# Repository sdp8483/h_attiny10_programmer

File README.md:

# ATTINY10 High Voltage Programmer
based on design from Ben Hecks video: https://www.youtube.com/watch?v=ra7bT74EGUs&t=913s

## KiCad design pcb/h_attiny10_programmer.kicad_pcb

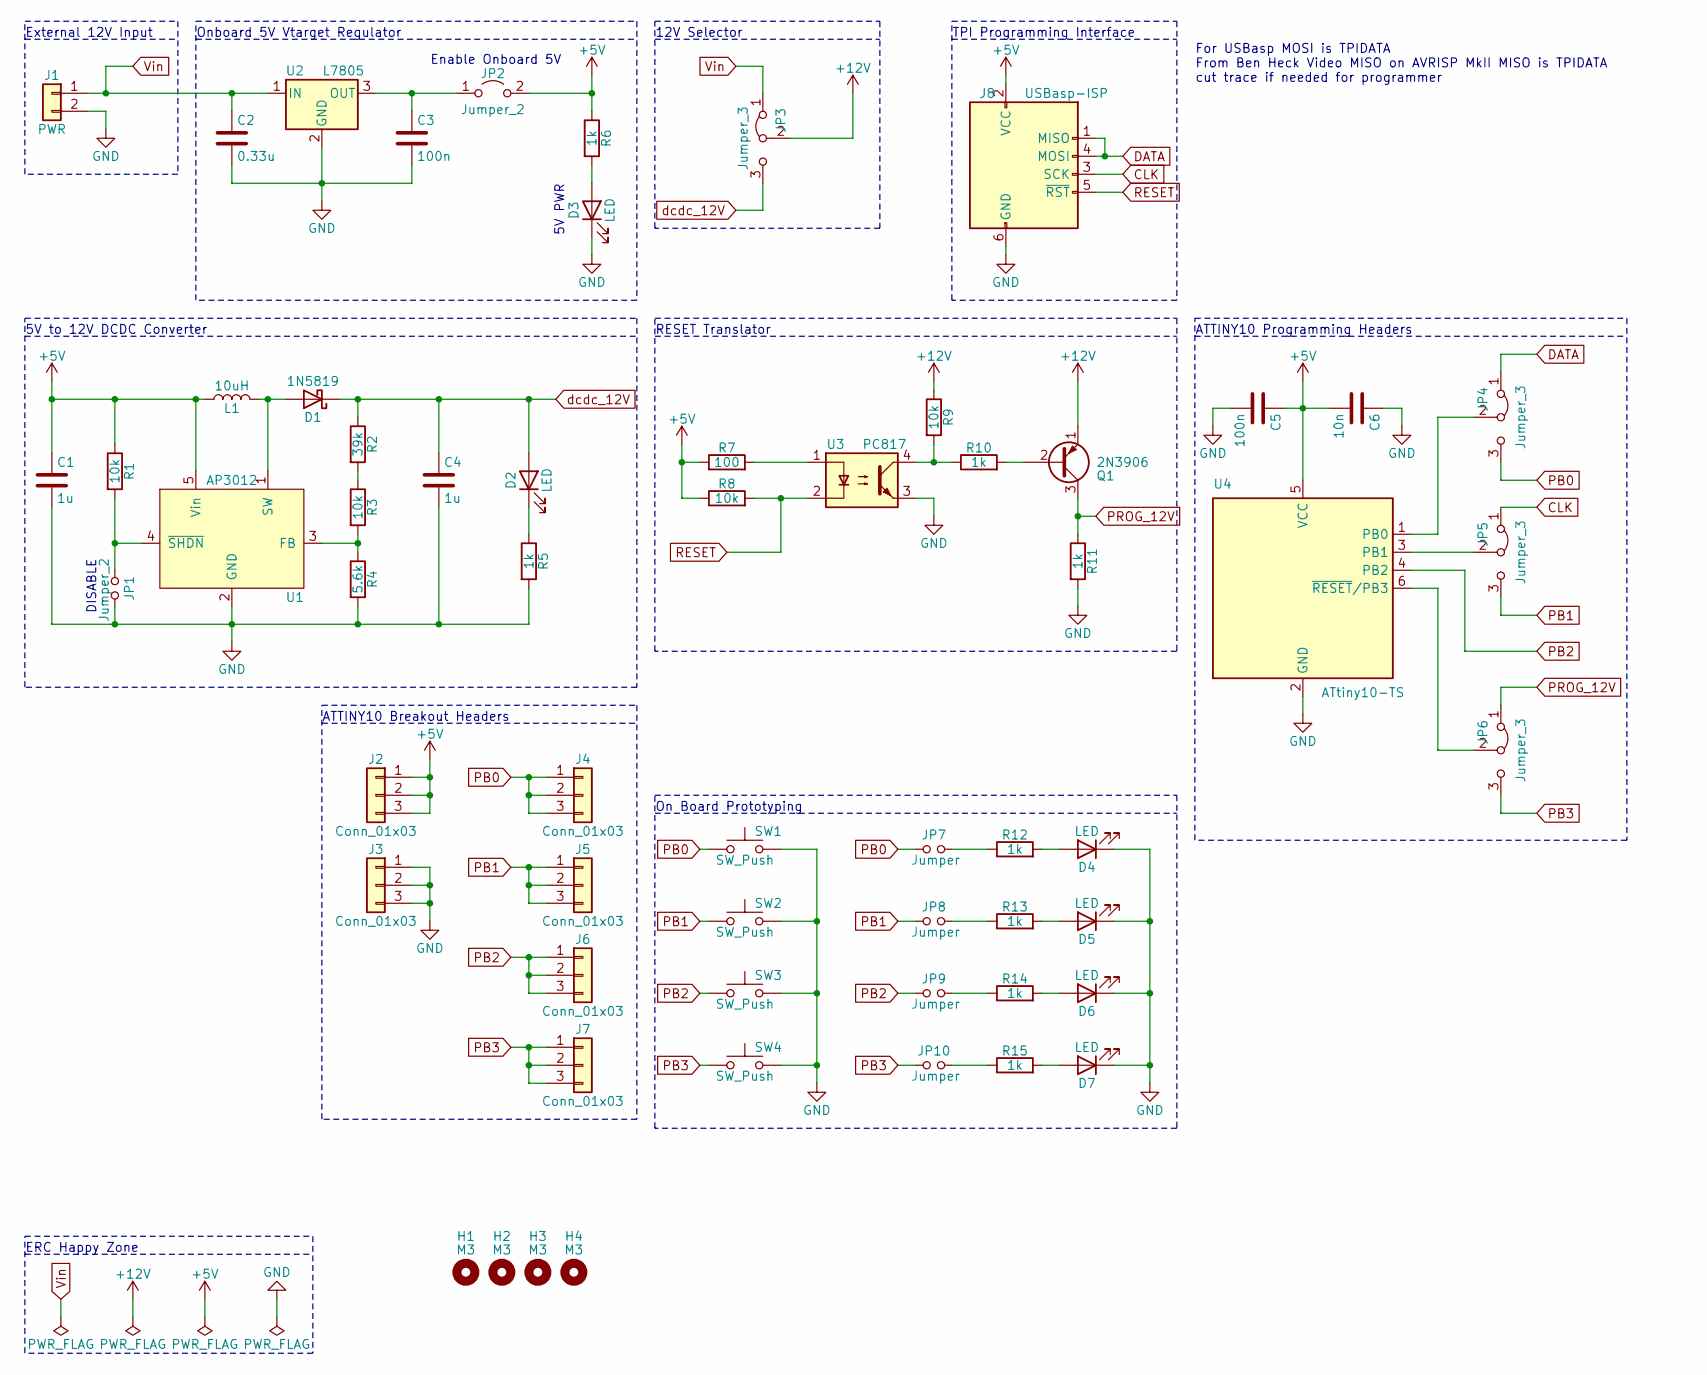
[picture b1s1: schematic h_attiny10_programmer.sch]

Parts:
C1, C4: 1u; C_0805_2012Metric_Pad1.18x1.45mm_HandSolder
C2: 0.33u; CP_Radial_D5.0mm_P2.50mm
C3: 100n; C_Disc_D4.3mm_W1.9mm_P5.00mm
C5: 100n; C_0805_2012Metric_Pad1.18x1.45mm_HandSolder
C6: 10n; C_0805_2012Metric_Pad1.18x1.45mm_HandSolder
D1: 1N5819; D_DO-41_SOD81_P10.16mm_Horizontal
D2, D3, D4, D5, D6, D7: LED; LED_D5.0mm
H1, H2, H3, H4: M3; MountingHole_3.5mm
J1: PWR; TerminalBlock_bornier-2_P5.08mm
J2, J3, J4, J5, J6, J7: Conn_01x03; PinHeader_1x03_P2.54mm_Vertical
J8: USBasp-ISP; PinHeader_2x03_P2.54mm_Vertical
JP1, JP2: Jumper_2; PinHeader_1x02_P2.54mm_Vertical
JP3, JP4, JP5, JP6: Jumper_3; PinHeader_1x03_P2.54mm_Vertical
JP7, JP8, JP9, JP10: Jumper; PinHeader_1x02_P2.54mm_Vertical
L1: 10uH; sumida_cdrh2d11
Q1: 2N3906; TO-92_Inline_Wide
R1, R3, R8, R9: 10k; R_Axial_DIN0207_L6.3mm_D2.5mm_P10.16mm_Horizontal
R2: 39k; R_Axial_DIN0207_L6.3mm_D2.5mm_P10.16mm_Horizontal
R4: 5.6k; R_Axial_DIN0207_L6.3mm_D2.5mm_P10.16mm_Horizontal
R5, R6, R10, R11, R12, R13, R14, R15: 1k; R_Axial_DIN0207_L6.3mm_D2.5mm_P10.16mm_Horizontal
R7: 100; R_Axial_DIN0207_L6.3mm_D2.5mm_P10.16mm_Horizontal
SW1, SW2, SW3, SW4: SW_Push; SW_PUSH_6mm
U1: AP3012; SOT-23-5
U2: L7805; TO-220-3_Vertical
U3: PC817; DIP-4_W7.62mm
U4: ATtiny10-TS; DIP-6_W7.62mm

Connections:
+5V: C1.1, C5.1, C6.2, J2.1, J2.2, J2.3, J8.2 (VCC), JP2.2 (B), L1.2, R1.1, R6.1, R7.1, R8.1, U1.5 (Vin), U4.5 (VCC)
+12V: JP3.2 (C), Q1.1 (E), R9.1
CLK: J8.3 (SCK), JP5.1 (A)
DATA: J8.1 (MISO), J8.4 (MOSI), JP4.1 (A)
GND: C1.2, C2.2, C3.2, C4.2, C5.2, C6.1, D3.1 (K), D4.1 (K), D5.1 (K), D6.1 (K), D7.1 (K), J1.2, J3.1, J3.2, J3.3, J8.6 (GND), JP1.2, R4.2, R5.2, R11.2, SW1.2, SW2.2, SW3.2, SW4.2, U1.2 (GND), U2.2 (GND), U3.3, U4.2 (GND)
unnamed: C3.1, JP2.1 (A), U2.3 (OUT)
unnamed: D1.2 (A), L1.1, U1.1 (SW)
unnamed: D2.1 (K), R5.1
unnamed: D3.2 (A), R6.2
unnamed: D4.2 (A), R12.2
unnamed: D5.2 (A), R13.2
unnamed: D6.2 (A), R14.2
unnamed: D7.2 (A), R15.2
unnamed: JP1.1, R1.2, U1.4 (~SHDN)
unnamed: JP4.2 (C), U4.1 (PB0)
unnamed: JP5.2 (C), U4.3 (PB1)
unnamed: JP6.2 (C), U4.6 (~RESET~/PB3)
unnamed: JP7.2, R12.1
unnamed: JP8.2, R13.1
unnamed: JP9.2, R14.1
unnamed: JP10.2, R15.1
unnamed: Q1.2 (B), R10.2
unnamed: R2.2, R3.1
unnamed: R3.2, R4.1, U1.3 (FB)
unnamed: R7.2, U3.1
unnamed: R9.2, R10.1, U3.4
PB0: J4.1, J4.2, J4.3, JP4.3 (B), JP7.1, SW1.1
PB1: J5.1, J5.2, J5.3, JP5.3 (B), JP8.1, SW2.1
PB2: J6.1, J6.2, J6.3, JP9.1, SW3.1, U4.4 (PB2)
PB3: J7.1, J7.2, J7.3, JP6.3 (B), JP10.1, SW4.1
PROG_12V: JP6.1 (A), Q1.3 (C), R11.1
RESET: J8.5 (~RST), R8.2, U3.2
Vin: C2.1, J1.1, JP3.1 (A), U2.1 (IN)
dcdc_12V: C4.1, D1.1 (K), D2.2 (A), JP3.3 (B), R2.1

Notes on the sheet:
External 12V Input
Onboard 5V Vtarget Regulator
5V to 12V DCDC Converter
12V Selector
5V PWR
Enable Onboard 5V
ATTINY10 Programming Headers
RESET Translator
TPI Programming Interface
ATTINY10 Breakout Headers
On Board Prototyping
DISABLE
ERC Happy Zone
For USBasp MOSI is TPIDATA From Ben Heck Video MISO on AVRISP MkII MISO is TPIDATA cut trace if needed for programmer

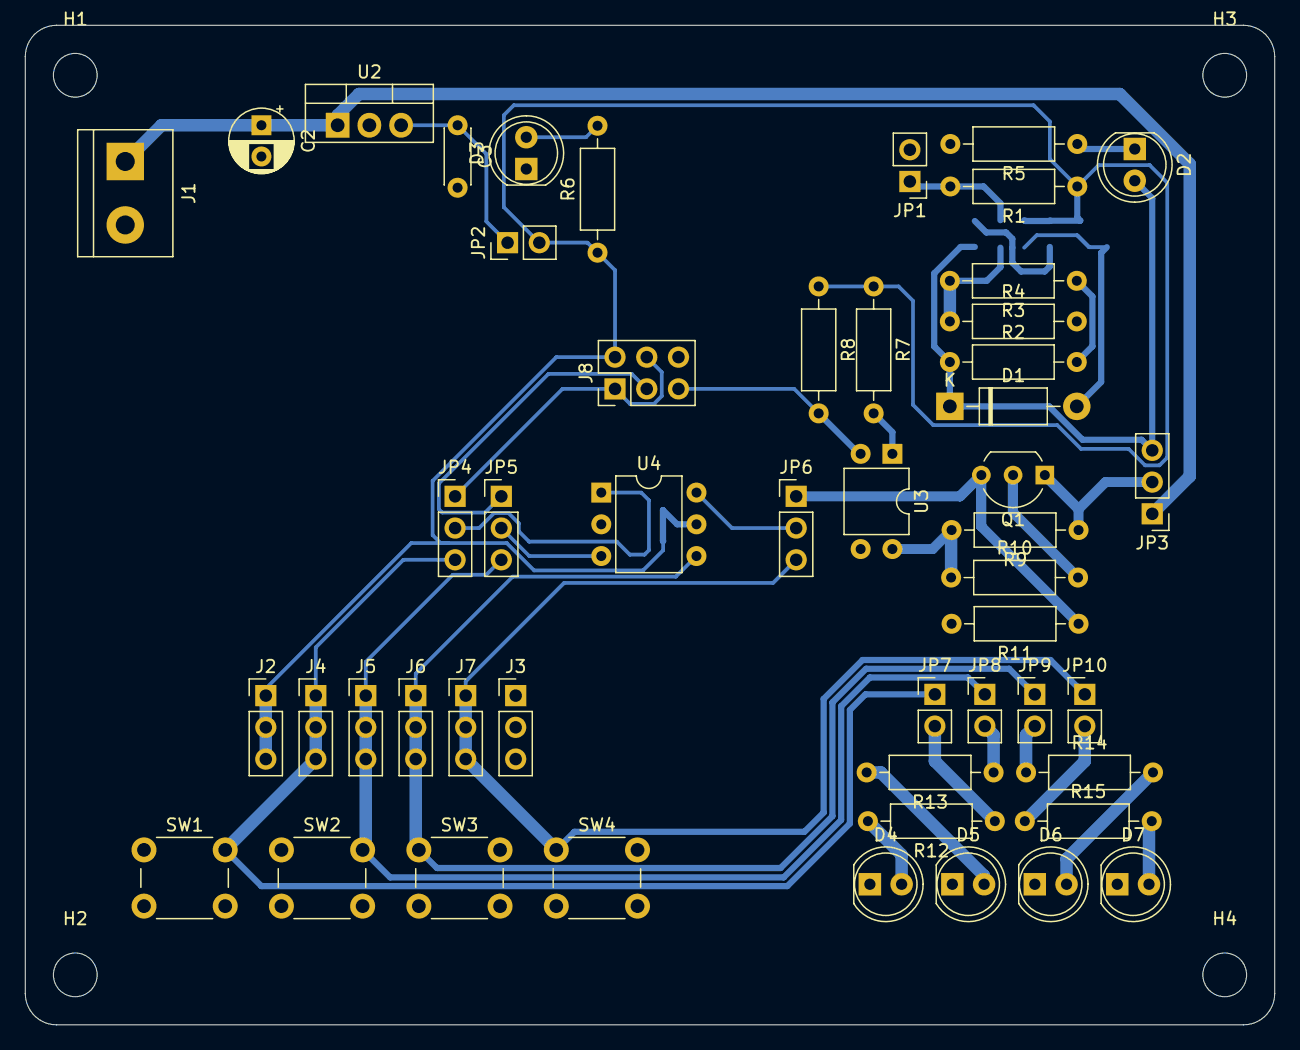
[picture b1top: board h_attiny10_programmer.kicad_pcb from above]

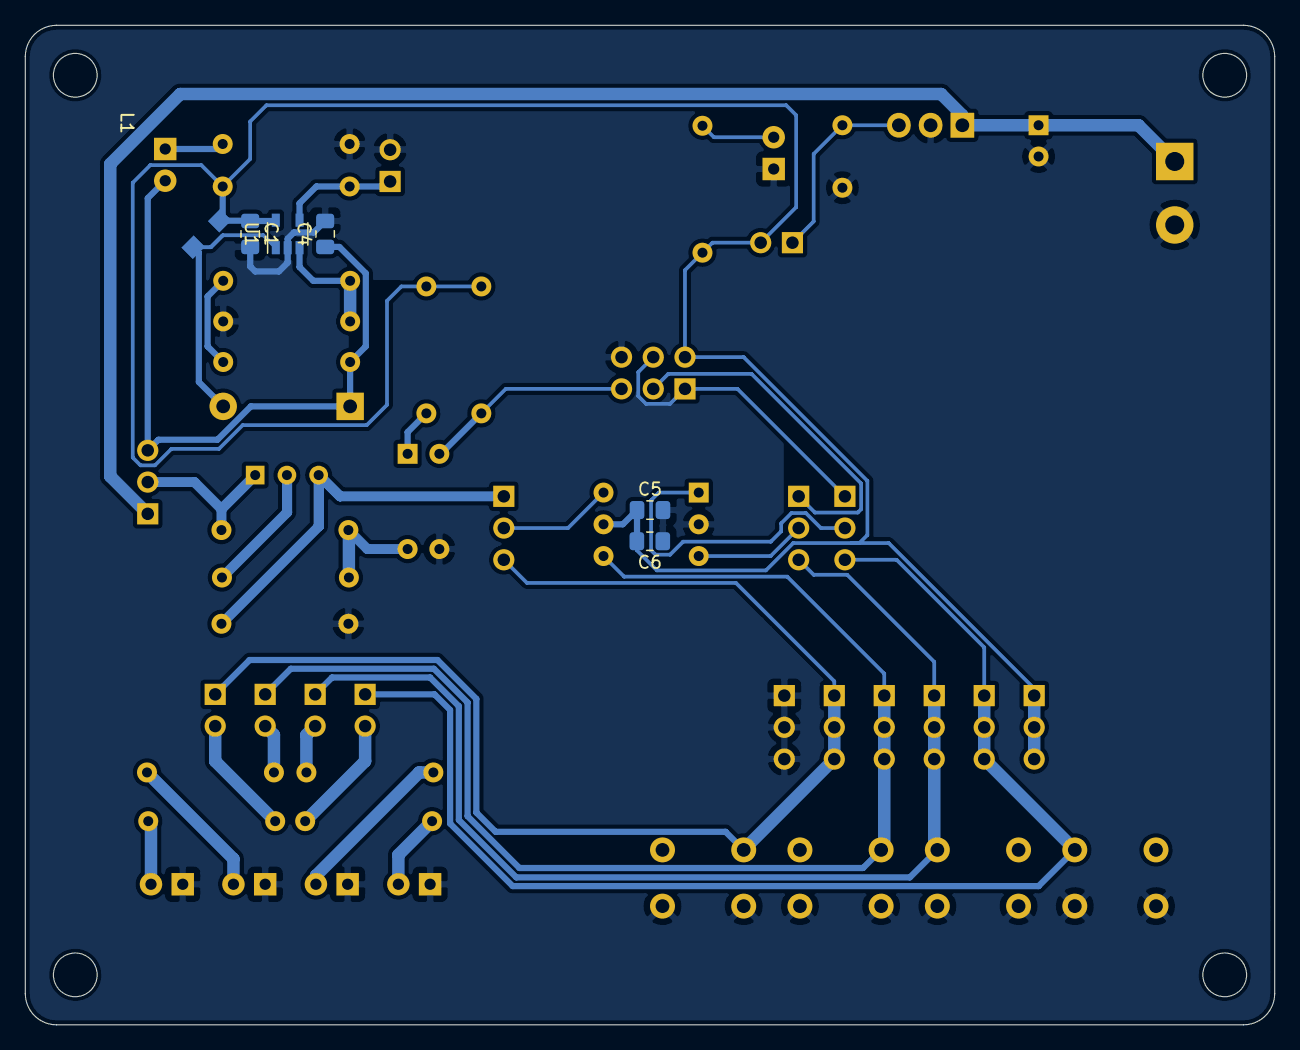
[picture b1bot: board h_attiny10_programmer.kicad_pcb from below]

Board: 2 copper layers, 100.0 x 80.0 mm, 60 parts (6 on the bottom side), 34 nets.

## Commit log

2020-12-12 initi empty commit
2020-12-13 create schematic
2020-12-13 change DCDC converter
2020-12-13 change ATTINY10 footprint to DIP-6 for breakout
2020-12-13 vin change to terminal block
2020-12-13 change attiny10 capacitor footprint to smd
2020-12-13 pcb layout
2020-12-13 clean up layout
2020-12-13 add aux axis
2020-12-13 output gerbers
2020-12-14 create cnc gcode
2020-12-14 output schematic to pdf
2020-12-14 PNP incorrect orientaiton, mirrored along x axis in schematic to fix
2020-12-19 connect TPIDATA to MISO and MOSI
